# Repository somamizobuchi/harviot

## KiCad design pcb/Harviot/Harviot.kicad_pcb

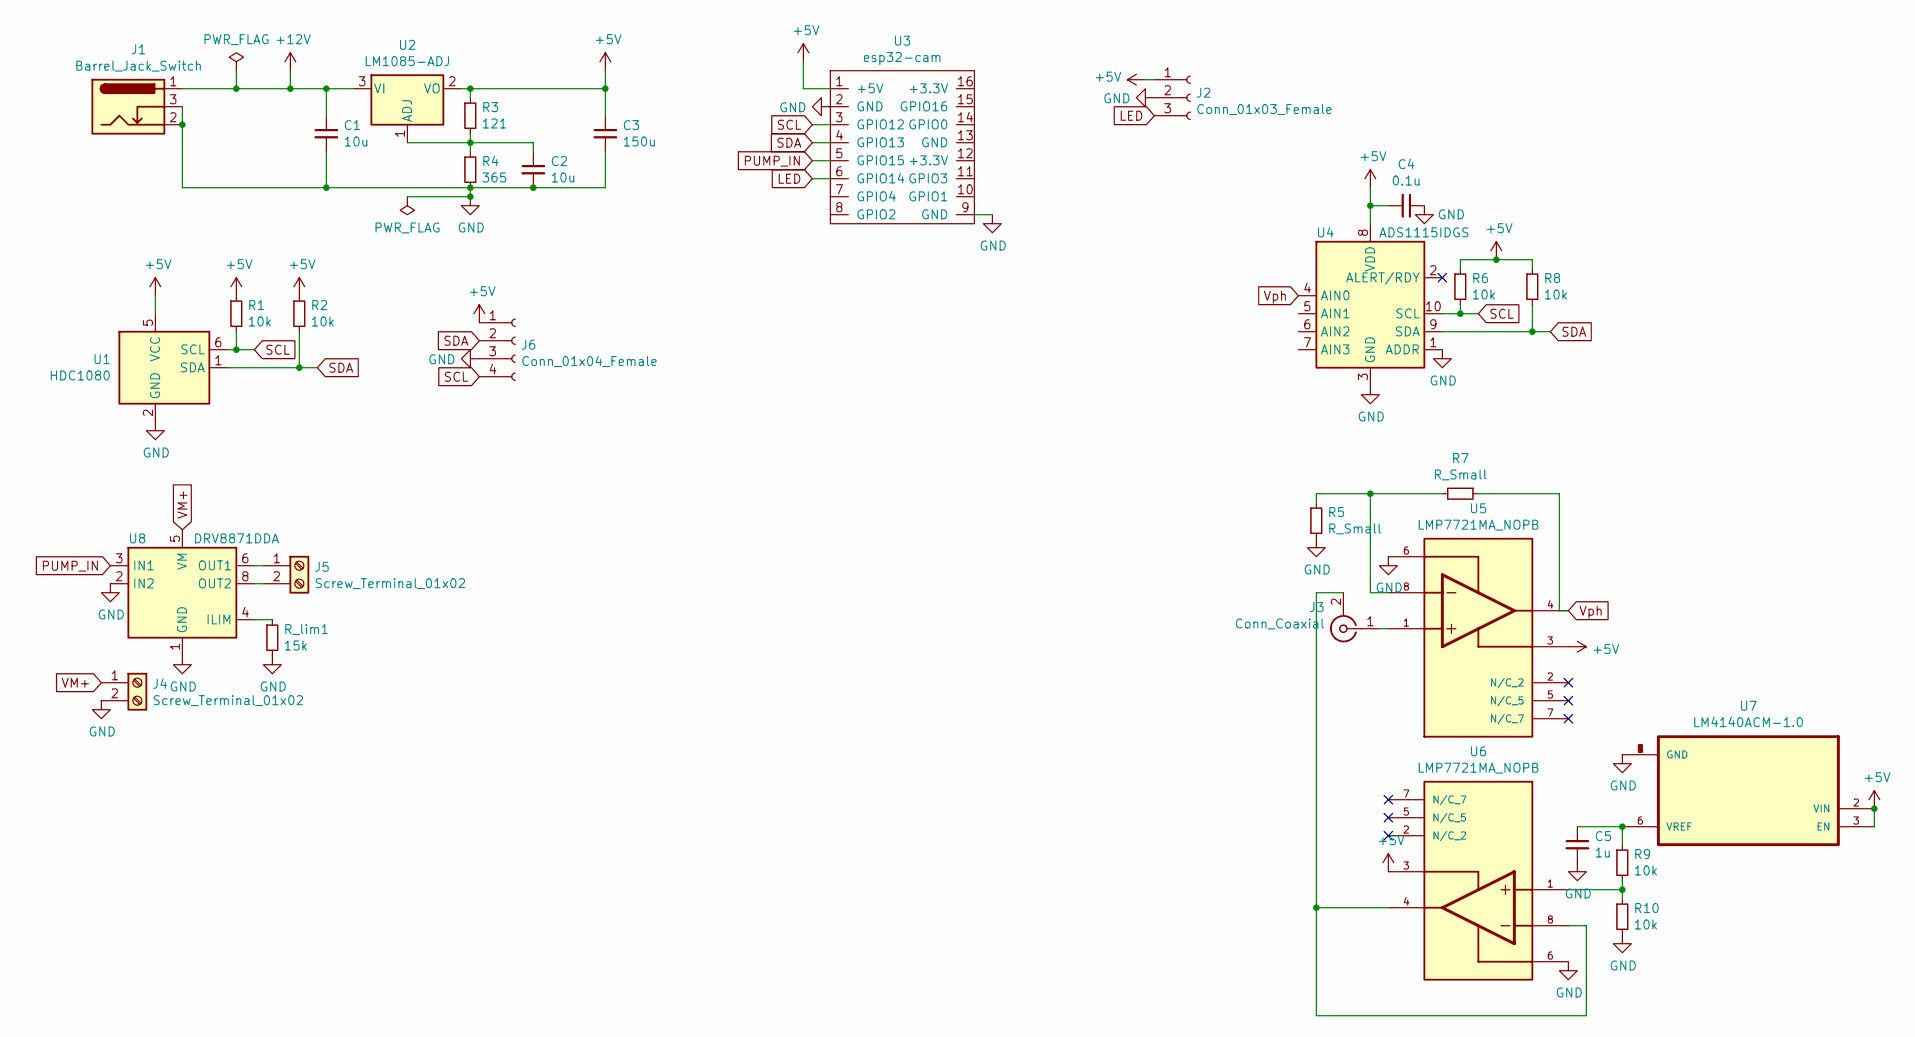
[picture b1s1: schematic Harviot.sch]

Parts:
C1, C2: 10u; CP_Radial_D6.3mm_P2.50mm
C3: 150u; CP_Radial_D6.3mm_P2.50mm
C4: 0.1u; C_0603_1608Metric
C5: 1u; C_0603_1608Metric
J1: Barrel_Jack_Switch; BarrelJack_Horizontal
J2: Conn_01x03_Female; PinSocket_1x03_P2.54mm_Horizontal
J3: Conn_Coaxial; RF_SMA_RightAngle_5-1814400-1
J4, J5: Screw_Terminal_01x02; TerminalBlock_Phoenix_MKDS-1,5-2_1x02_P5.00mm_Horizontal
J6: Conn_01x04_Female; JST_EH_S4B-EH_1x04_P2.50mm_Horizontal
R1, R2, R6, R8, R9, R10: 10k; R_0603_1608Metric
R3: 121; R_0603_1608Metric
R4: 365; R_0603_1608Metric
R5, R7: R_Small; R_0603_1608Metric
R_lim1: 15k; R_0603_1608Metric
U1: HDC1080; Texas_PWSON-N6
U2: LM1085-ADJ; TO-220-3
U3: esp32-cam
U4: ADS1115IDGS; TSSOP-10_3x3mm_P0.5mm
U5, U6: LMP7721MA_NOPB; SOIC127P599X175-8N; PARTREV E
U7: LM4140ACM-1.0; SOIC127P599X175-8N
U8: DRV8871DDA; Texas_HTSOP-8-1EP_3.9x4.9mm_P1.27mm_EP2.95x4.9mm_Mask2.4x3.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

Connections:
+5V: C3.1, C4.2, J2.1, J6.1, R1.1, R2.1, R3.1, R6.1, R8.1, U1.5 (VCC), U2.2 (VO), U3.1 (+5V), U4.8 (VDD), U5.3, U6.3, U7.2 (VIN), U7.3 (EN)
+12V: C1.1, J1.1, U2.3 (VI)
GND: C1.2, C2.2, C3.2, C4.1, C5.2, J1.2, J1.3, J2.2, J4.2, J6.3, R4.2, R5.2, R10.2, R_lim1.2, U1.2 (GND), U3.2 (GND), U3.9 (GND), U4.1 (ADDR), U4.3 (GND), U5.6, U6.6, U7.1 (GND), U7.4 (GND), U7.7 (GND), U7.8 (GND), U8.1 (GND), U8.2 (IN2), U8.7 (GND), U8.9 (GND)
LED: J2.3, U3.6 (GPIO14)
unnamed: C2.1, R3.2, R4.1, U2.1 (ADJ)
unnamed: C5.1, R9.1, U7.6 (VREF)
unnamed: J3.1 (In), U5.1
unnamed: J3.2 (Ext), U6.4, U6.8
unnamed: J5.1, U8.6 (OUT1)
unnamed: J5.2, U8.8 (OUT2)
unnamed: R5.1, R7.2, U5.8
unnamed: R9.2, R10.1, U6.1
unnamed: R_lim1.1, U8.4 (ILIM)
PUMP_IN: U3.5 (GPIO15), U8.3 (IN1)
SCL: J6.4, R1.2, R6.2, U1.6 (SCL), U3.3 (GPIO12), U4.10 (SCL)
SDA: J6.2, R2.2, R8.2, U1.1 (SDA), U3.4 (GPIO13), U4.9 (SDA)
VM+: J4.1, U8.5 (VM)
Vph: R7.1, U4.4 (AIN0), U5.4

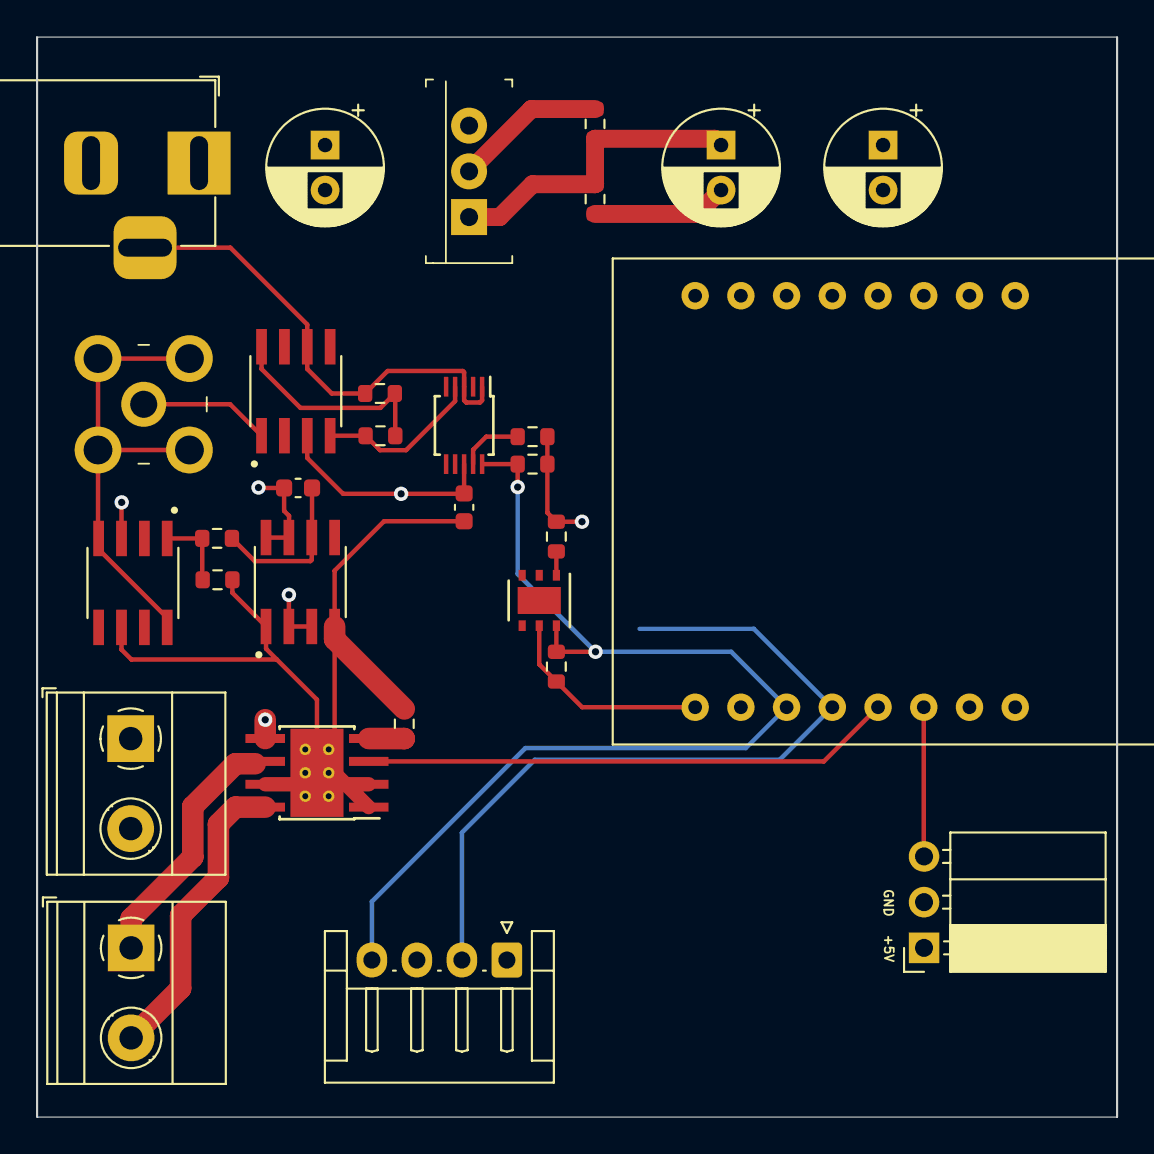
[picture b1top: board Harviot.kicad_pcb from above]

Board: 4 copper layers, 60.0 x 60.0 mm, 30 parts (0 on the bottom side), 18 nets.

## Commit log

2021-02-04 added .gitignore
2021-02-04 .gitignore updates
2021-02-04 gitignore
2021-02-04 server
2021-02-05 Mongoose Users model
2021-02-05 authentication added
2021-02-05 minor
2021-02-05 mardown to api home
2021-02-08 test route added
2021-02-08 ws debug message:
2021-02-08 ws port changed to 80
2021-02-08 ws port changed to 8080
2021-02-08 https rerouting
2021-02-08 temporarily disable certs
2021-02-08 ws message
2021-03-08 remove pem
2021-03-08 added esp32 code
2021-03-08 'web' dir renamed to 'server'
2021-03-08 user login updated
2021-03-08 removed login static
2021-03-08 new user methods
2021-03-08 added owner field to Plant schema
2021-03-10 Fixed Plant model bug
2021-03-11 Add mesees
2021-03-11 New commit
2021-03-11 latest
2021-03-11 update gitignore
2021-03-30 added firstname lastname fields to user model
2021-03-31 cors capabilities added
2021-04-12 or operator fix
2021-04-16 Initial commit for ESP32 PlatformIO migration
2021-04-26 cors option for all origins added
2021-04-26 added dialogue for ws connection without plant_id
2021-04-26 migration to platformio complete
2021-04-29 Post and get methods added
2021-04-29 Logs schema and field created
2021-04-29 Logging functionality added
2021-04-29 Sensor reading and logging added as seudo-threaded operation
2021-04-29 Slide bar for RGB Light color added
2021-04-29 Time.h added
2021-05-02 Plant routes modified
2021-05-03 cors mods
2021-05-03 request headers changed
2021-05-03 minor request changes
2021-05-03 Test locally
2021-05-03 ws error handling
2021-05-03 updated register
2021-05-03 updated register signup
2021-05-03 wreconnection feature added
2021-05-03 ssl implementation
2021-05-03 secure implementations
2021-05-13 image upload added
2021-05-13 s3 + multer image upload
2021-05-13 KiCAD
2021-05-13 removed all websockets implementation
2021-05-22 frontent reset
2021-05-22 new class structures
2021-05-22 Webpack/React setup boilerplate
2021-05-23 typescript setup
